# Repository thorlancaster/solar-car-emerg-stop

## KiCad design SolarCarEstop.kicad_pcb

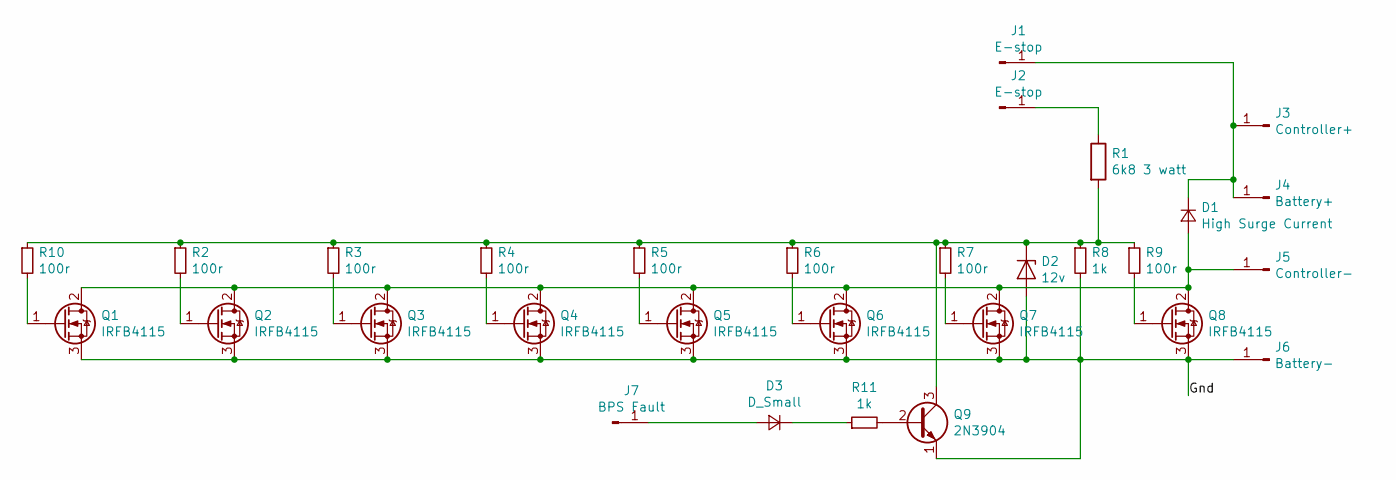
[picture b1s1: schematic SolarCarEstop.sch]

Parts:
D1: High Surge Current; D_5W_P12.70mm_Horizontal
D2: 12v; D_5W_P12.70mm_Horizontal
D3: D_Small; D_5W_P12.70mm_Horizontal
J1, J2: E-stop; SolderWirePad_1x01_Drill1.2mm
J3: Controller+; SolderWirePad_1x01_Drill2.5mm
J4: Battery+; SolderWirePad_1x01_Drill2.5mm
J5: Controller-; SolderWirePad_1x01_Drill2.5mm
J6: Battery-; SolderWirePad_1x01_Drill2.5mm
J7: BPS Fault; SolderWirePad_1x01_Drill1.2mm
Q1, Q2, Q3, Q4, Q5, Q6, Q7, Q8: IRFB4115; TO-220-3_Vertical
Q9: 2N3904; TO-92_Inline
R1: 6k8 3 watt; R_Axial_DIN0918_L18.0mm_D9.0mm_P25.40mm_Horizontal
R2, R3, R4, R5, R6, R7, R9, R10: 100r; R_Axial_DIN0204_L3.6mm_D1.6mm_P7.62mm_Horizontal
R8, R11: 1k; R_Axial_DIN0204_L3.6mm_D1.6mm_P7.62mm_Horizontal

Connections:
/Gnd: D2.2 (A), J6.1, Q1.3 (S), Q2.3 (S), Q3.3 (S), Q4.3 (S), Q5.3 (S), Q6.3 (S), Q7.3 (S), Q8.3 (S), Q9.1 (E), R8.2
unnamed: D1.1 (K), J1.1, J3.1, J4.1
unnamed: D1.2 (A), J5.1, Q1.2 (D), Q2.2 (D), Q3.2 (D), Q4.2 (D), Q5.2 (D), Q6.2 (D), Q7.2 (D), Q8.2 (D)
unnamed: D2.1 (K), Q9.3 (C), R1.2, R2.1, R3.1, R4.1, R5.1, R6.1, R7.1, R8.1, R9.1, R10.1
unnamed: D3.1 (K), R11.1
unnamed: D3.2 (A), J7.1
unnamed: J2.1, R1.1
unnamed: Q1.1 (G), R10.2
unnamed: Q2.1 (G), R2.2
unnamed: Q3.1 (G), R3.2
unnamed: Q4.1 (G), R4.2
unnamed: Q5.1 (G), R5.2
unnamed: Q6.1 (G), R6.2
unnamed: Q7.1 (G), R7.2
unnamed: Q8.1 (G), R9.2
unnamed: Q9.2 (B), R11.2

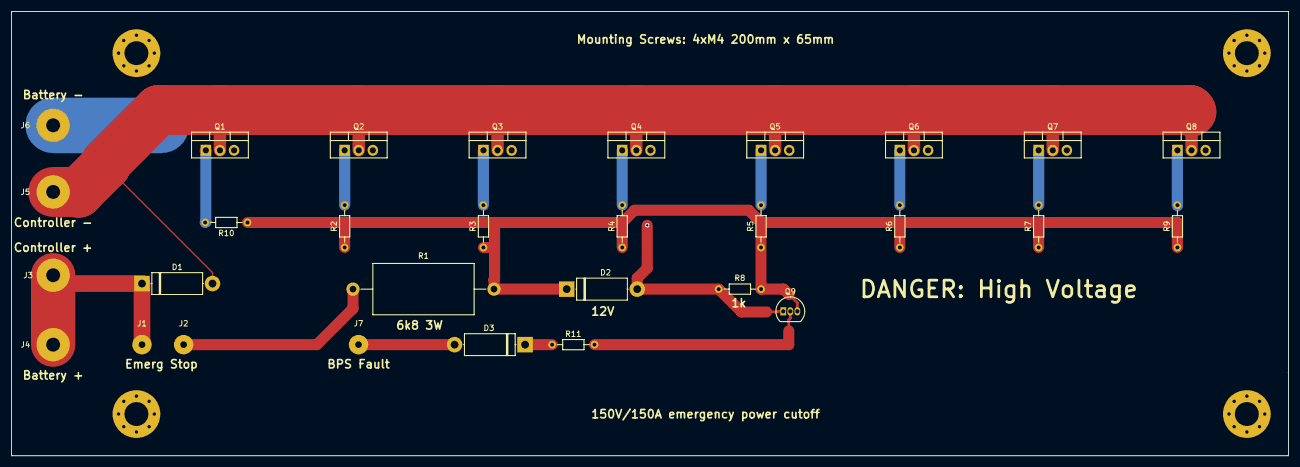
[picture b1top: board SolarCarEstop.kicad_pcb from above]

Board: 2 copper layers, 230.0 x 80.0 mm, 30 parts (0 on the bottom side), 16 nets.

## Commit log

2020-09-29 Add buck converter and 555 charge pump
2020-10-09 Add emergency button, BMS fault output, and BMS fault input
